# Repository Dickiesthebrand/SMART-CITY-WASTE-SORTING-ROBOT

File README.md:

# SMART CITY WASTE SORTING ROBOT

Group Members and roles:

1. Dickson Mbogo - Program Developer
2. Elisha Jilo - Electrical Systems Developer
3. Shem Koech - Mechanical Designer
4. Masika - Supervisor

Overview
An autonomous system that classifies waste into three types—metal, plastic, and organic—using sensors and sorts them using three servo motors, each linked to a dedicated bin.

 Working
Detection:

Object placed on input chute.

Sensors analyze:

Inductive sensor → detects metal.

IR sensor → detects plastic.

Moisture sensor → detects organic.

Decision:

Microcontroller reads sensor output.

Decides which servo to activate.

Sorting:
https://trello.com/invite/b/67b381944852fa081ac035bd/ATTI09b28d262ff8065e7019820daa05c8408FD4BF4F/smart-city
trello link

Servo 1 rotates chute to bin 1 for metal.

Servo 2 rotates chute to bin 2 for plastic.

Servo 3 rotates chute to bin 3 for organic.

Reset:

Chute returns to initial position.

Waits for next input.

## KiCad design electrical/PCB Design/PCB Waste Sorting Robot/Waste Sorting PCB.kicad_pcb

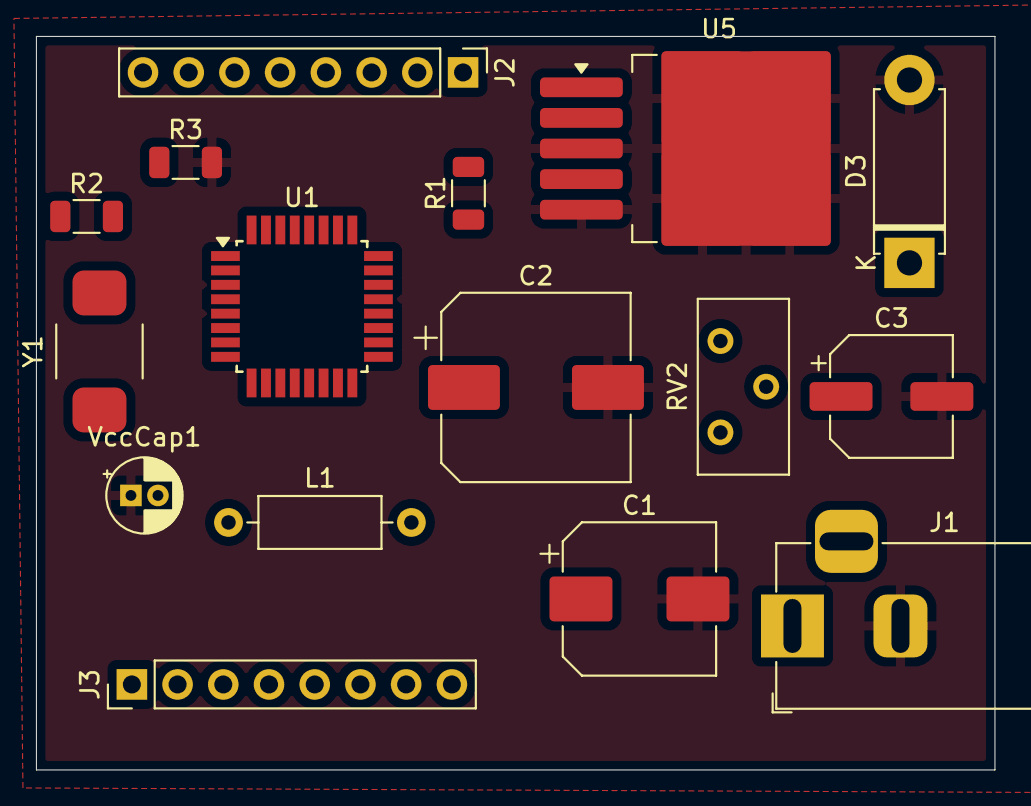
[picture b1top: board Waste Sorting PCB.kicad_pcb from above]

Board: 2 copper layers, 53.2 x 40.8 mm, 16 parts (0 on the bottom side), 28 nets, no tracks yet.

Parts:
C1: 100u; CP_Elec_8x10
C2: 220u; CP_Elec_10x10
C3: 100u; CP_Elec_6.3x5.4
D3: 1N5822; D_5W_P10.16mm_Horizontal
J1: Barrel_Jack; BarrelJack_Horizontal
J2, J3: Conn_01x08_Pin; PinHeader_1x08_P2.54mm_Vertical
L1: L; L_Axial_L6.6mm_D2.7mm_P10.16mm_Horizontal_Vishay_IM-2
R1, R3: 1.21 k; R_1206_3216Metric
R2: R; R_1206_3216Metric
RV2: 50 k; Potentiometer_Bourns_3296Y_Vertical
U1: ATmega328-A; TQFP-32_7x7mm_P0.8mm
U5: LM2596S-ADJ; TO-263-5_TabPin3
VccCap1: C; CP_Radial_D4.0mm_P1.50mm
Y1: Crystal; Crystal_SMD_TXC_AX_8045-2Pin_8.0x4.5mm

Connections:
+5V: C3.1, L1.1, U1.4 (VCC), U1.6 (VCC), VccCap1.2
GND: C1.2, C2.2, C3.2, D3.2 (A), J1.2, R3.2, U1.3 (GND), U1.5 (GND), U1.21 (GND), U5.3 (GND), U5.5 (~ON/OFF), VccCap1.1
unnamed: C2.1, RV2.1
unnamed: R2.1, U1.17 (PB5)
unnamed: D3.1 (K), U5.2 (OUT)
unnamed: J2.1, U1.30 (PD0)
unnamed: J2.2, U1.31 (PD1)
unnamed: J2.3, U1.32 (PD2)
unnamed: J2.4, U1.1 (PD3)
unnamed: J2.5, U1.2 (PD4)
unnamed: J2.6, U1.9 (PD5)
unnamed: J2.7, U1.10 (PD6)
unnamed: J2.8, U1.11 (PD7)
unnamed: J3.1, U1.8 (XTAL2/PB7)
unnamed: J3.2, U1.23 (PC0)
unnamed: J3.3, U1.24 (PC1)
unnamed: J3.4, U1.25 (PC2)
unnamed: J3.5, U1.26 (PC3)
unnamed: J3.6, U1.27 (PC4)
unnamed: J3.7, U1.28 (PC5)
unnamed: J3.8, U1.29 (~RESET/PC6)
unnamed: R3.1, RV2.3
unnamed: L1.2, U1.18 (AVCC)
unnamed: U1.12 (PB0), Y1.2
unnamed: U1.13 (PB1), Y1.1
unnamed: R1.1, U1.7 (XTAL1/PB6)
unnamed: RV2.2, U5.4 (FB)
unnamed: C1.1, J1.1, U5.1 (VIN)

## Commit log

2025-06-17 Initial commit: project setup
2025-06-17 commit 1
2025-06-18 Add electrical subsystem
2025-06-18 Add main assembly archive and reference image to mechanical branch
2025-06-18 Create Template
2025-06-22 Update of mechanical design version 2
2025-06-22 add pcb file
2025-06-23 Added PCB
